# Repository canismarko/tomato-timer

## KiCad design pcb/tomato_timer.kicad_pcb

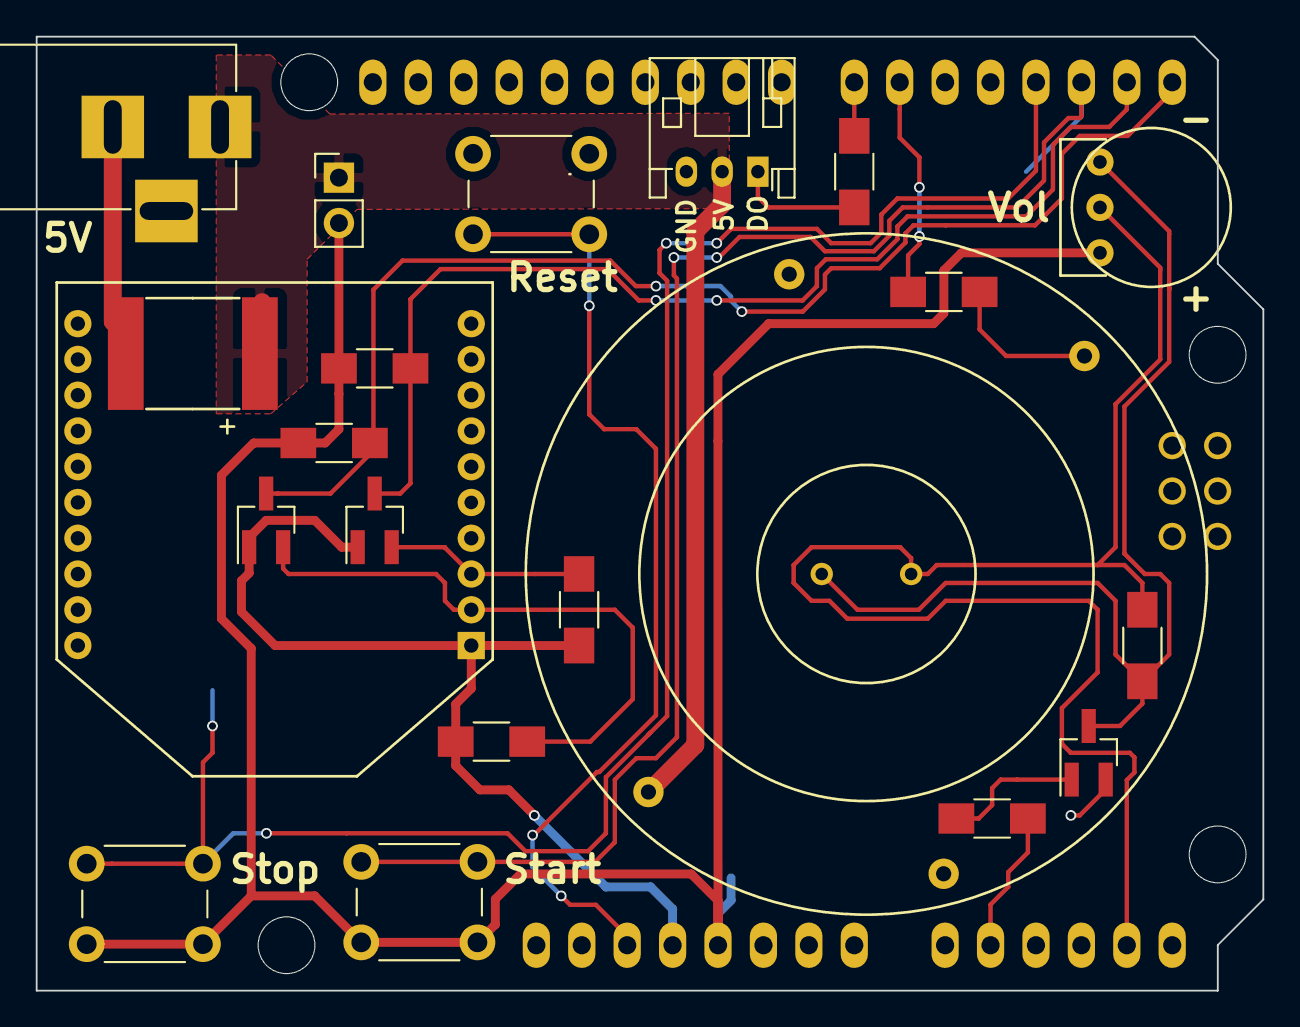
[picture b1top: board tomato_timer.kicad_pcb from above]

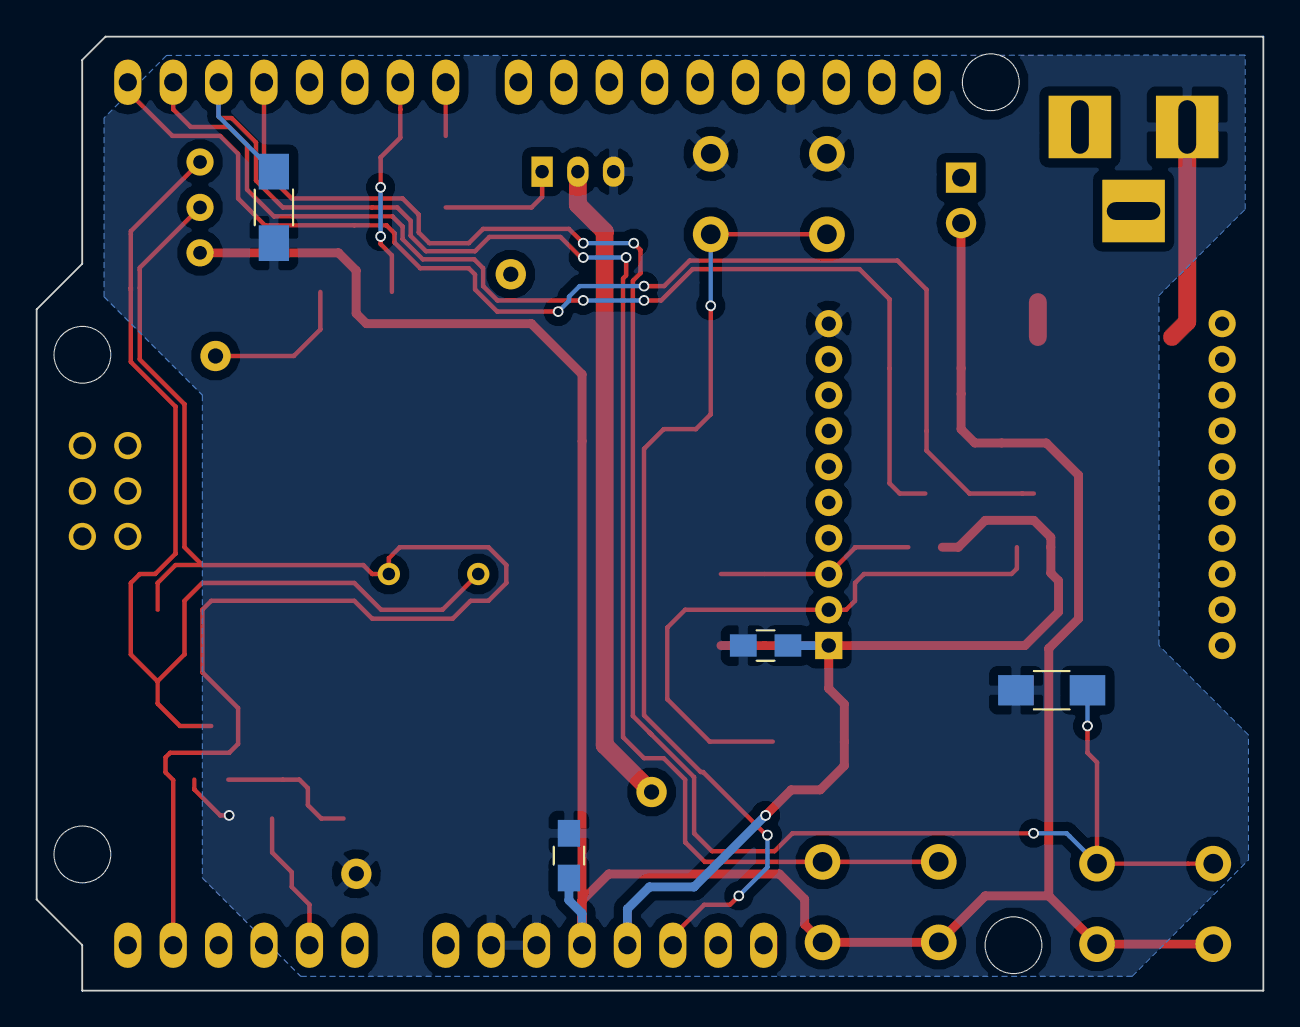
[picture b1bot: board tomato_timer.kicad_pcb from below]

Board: 2 copper layers, 68.6 x 53.3 mm, 27 parts (4 on the bottom side), 19 nets.

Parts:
C1, C3: 0.1uF; C_0805_HandSoldering
C2: 1000uF; SMD-2824
D1: NeoPixel_Strip; JST_PH_S3B-PH-K_03x2.00mm_Angled
D2: NeoPixelRing; NeoPixelRing_12
J1: External_Power; BARREL_JACK
JP2: Jumper_2_Open; Pin_Header_Straight_1x02_Pitch2.54mm
LS1: Speaker_Crystal; Buzzer160
Q1, Q2: BSS138; SOT-23_Handsoldering
Q3: TRANSISTOR_NPN; MMBT6428LT1G_NPN
R1, R2, R3, R4, R5, R6, R9: 10K; R_1206_HandSoldering
R7, R8: 470; R_1206_HandSoldering
R10: 1K; R_1206_HandSoldering
RV1: 10K; Whell_Potentiometer_3352T
SW2: SW_Reset; SW_PUSH_6mm
SW3: SW_Start; SW_PUSH_6mm
SW4: SW_Stop; SW_PUSH_6mm
TOMATO_SHIELD1: ARDUINO_SHIELD
U1: XBeeSeries1; XBee802.154.4

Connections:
/3V3: C1.2, Q1.1, Q2.1, R2.2, R4.2, TOMATO_SHIELD1.3V3, U1.1
/5V: C3.2, JP2.2, R1.1, R3.1, RV1.3, SW3.1, SW4.1, TOMATO_SHIELD1.5V
/5V_IN: C2.1, D1.2, D2.3, J1.1, JP2.1
/BTN_START: R5.1, SW3.2, TOMATO_SHIELD1.2
/BTN_STOP: R6.1, SW4.2, TOMATO_SHIELD1.3
/BUZZER: R9.1, TOMATO_SHIELD1.AD1
/DIN: Q1.2, R2.1, U1.3
/DOUT: Q2.2, R4.1, U1.2
/GND: C1.1, C2.2, C3.1, D1.3, D2.2, J1.2, Q3.E, R5.2, R6.2, SW2.2, TOMATO_SHIELD1.GND1, TOMATO_SHIELD1.GND2, TOMATO_SHIELD1.GND3, U1.10
/PIXEL_RING_PIN: R7.2, TOMATO_SHIELD1.6
/PIXEL_STRIP_PIN: R8.2, TOMATO_SHIELD1.7
/RESET: SW2.1, TOMATO_SHIELD1.RST
/RX: Q2.3, R3.2, TOMATO_SHIELD1.0
/TX: Q1.3, R1.2, TOMATO_SHIELD1.1
/VOL_IN: LS1.2, R10.1, RV1.2, TOMATO_SHIELD1.AD4
unnamed: D1.1, R8.1
unnamed: D2.4, R7.1
unnamed: LS1.1, Q3.C, R10.2, RV1.1
unnamed: Q3.B, R9.2

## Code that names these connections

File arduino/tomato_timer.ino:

/*
  Tomato Timer

  Creates a countdown timer for staying on track during boring work.

  Exampes usage: work for 25 min, then break for 5,
  then work for 25, etc. Every 4 work periods,
  there is a longer 20 minutes break.

  January 2017
  Mark Wolf
*/

// Durations for each phase (in milliseconds)
// Eg. 5 * 60 * 1000 --> 5 min
#define TICK  400
#define DEBUG_SPEEDUP 1 // Set to 1 for normal operation
#define WORK_TIME 25 * 60 * 1000ul / DEBUG_SPEEDUP
#define BREAK_TIME 5 * 60 * 1000ul / DEBUG_SPEEDUP
#define BREAK_TIME_LONG BREAK_TIME * 4

#define TONE_HZ 200

// Possible states for the system
#define WORKING 0
#define BREAK 1
#define LONG_BREAK 2
#define EXPIRED 3
#define STOPPED 4

// Button and buzzer pin assignments
#define BTN_START 2
#define BTN_STOP 3
// #define BTN_PIN 2
// #define BTN_STOP 19
// #define MUTE_PIN 2
#define BUZZER A0

// LED pin assignments
#define RED0 7
#define RED1 5
#define RED2 4
#define RED3 6
#define RED4 8
#define GRN0 10
#define GRN1 11
#define GRN2 12
#define GRN3 13
#define GRN4 9

// Define pins for the red and green LED's
const int N_REDS = 5;
const int RED_PINS[N_REDS] = {RED0, RED1, RED2, RED3, RED4};
const int N_GRNS = 5;
const int GRN_PINS[N_GRNS] = {GRN0, GRN1, GRN2, GRN3, GRN4};

// Variable for keeping track of how long this round has been running
unsigned long startTime;

// Variable to keep track of which round of work we're on
unsigned long currentRound;
bool isStopped; // Are we currently paused
bool volatile btnPressed;
bool volatile useBuzzer;
bool volatile stopRequested; // Is the system waiting for a stop button handler

// Function to keep track of when the button was pressed
void press_button() {
  Serial.print("Start button pressed\n");
  btnPressed = true;
}

void stop_pressed() {
  Serial.print("Stop requested\n");
  stopRequested = true;
}

// Function for advancing to the next round of work
void start_next_round() {
  // Flash the lights to indicate the round number
  if (currentRound > 0) {
    sound_buzzer(LOW);
    writeRedPins(LOW);
    writeGreenPins(LOW);
    delay(TICK / 2);
    for (int i=0; i < currentRound; i += 1) {
      sound_buzzer(HIGH);
      writeRedPins(HIGH);
      writeGreenPins(HIGH);
      delay(TICK / 5);
      sound_buzzer(LOW);
      writeRedPins(LOW);
      writeGreenPins(LOW);
      delay(TICK);
    }
    writeRedPins(LOW);
    writeGreenPins(LOW);
    delay(TICK / 5);
  }
  // Log to serial console
  Serial.print("Advancing to round ");
  Serial.print(currentRound);
  Serial.print("\n");
  // Update state variables
  isStopped = false;
  currentRound += 1;
  startTime = millis();
  btnPressed = false;
  useBuzzer = true;
  // Turn off buzzer and pause for a moment
  noTone(BUZZER);
  delay(2*TICK);
  // Keep track of state
  isStopped = false;
}


// Global variable for whether to sound the buzzer (gets reset every round)
void mute_buzzer() {
  Serial.print("Silencing buzzer\n");
  useBuzzer = false;
}

// Function that either turns on or turns off the buzzer
void sound_buzzer(int state) {
  if (state == HIGH && useBuzzer) {
    tone(BUZZER, TONE_HZ);
  } else {
    noTone(BUZZER);
  }
}


// Function sets all pins in an array
void writeRedPins(int state) {
  for (int i = 0; i < N_REDS; i += 1) {
    digitalWrite(RED_PINS[i], state);
  }
}


// Function sets all pins in an array
void writeGreenPins(int state) {
  for (int i = 0; i < N_GRNS; i += 1) {
    digitalWrite(GRN_PINS[i], state);
  }
}


// Function that fluorishes the lights, then waits for the user to press the "Go" button
void pauseInit() {
  Serial.print("Pausing init\n");
  // Cycle through the lights
  char pins[] = {RED0, RED1, RED2, RED3, RED4, GRN3, GRN2, GRN1, GRN0, GRN4};
  int pause = 30;
  for (char i=0; i<10; i++) {
    digitalWrite(pins[i], HIGH);
    delay(pause);
    digitalWrite(pins[i], LOW);
  }
  for (char i=9; i>-1; i--) {
    digitalWrite(pins[i], HIGH);
    delay(pause);
    digitalWrite(pins[i], LOW);
  }

  // Wait for user to press the go button
  while (!btnPressed) {
    delay(100);
  }
}


// the setup function runs once when you press reset or power the board
void setup() {
  Serial.begin(9600);
  // initialize digital pin LED_BUILTIN as an output.
  for (int i = 0; i < N_REDS; i++) {
    pinMode(RED_PINS[i], OUTPUT);
  }
  for (int i = 0; i < N_GRNS; i++) {
    pinMode(GRN_PINS[i], OUTPUT);
  }

  // Set the interrupt for when the various buttons are pressed
  // attachInterrupt(digitalPinToInterrupt(MUTE_PIN), mute_buzzer, RISING);
  attachInterrupt(digitalPinToInterrupt(BTN_START), press_button, RISING);
  attachInterrupt(digitalPinToInterrupt(BTN_STOP), stop_pressed, RISING);

  // Start of on the first round
  currentRound = 0;

  // Wait for the user to press the go button
  pauseInit();

  // And away we gooooo....
  startTime = millis();
}

// Function that returns the current state based on elapsed time for this round
int currentState() {
  unsigned long elapsed = millis() - startTime;
  // Variable for holding the output
  int state;
  // Variable for how long the break should be this time around
  unsigned long round_time;
  // Variable for which break period we're in
  int break_type;
  if (currentRound % 4) {
    // Regular short break
    round_time = WORK_TIME + BREAK_TIME;
    break_type = BREAK;
  } else {
    // Every fourth round is a long break
    round_time = WORK_TIME + BREAK_TIME_LONG;
    break_type = LONG_BREAK;
  }
  // Now see what phase we're in based on how long we've been running
  if (isStopped) {
    state = STOPPED;
  } else if (elapsed < WORK_TIME) {
    // Just regular old working mode
    state = WORKING;
  } else if (elapsed < round_time) {
    // We're in a break
    state = break_type;
  } else {
    // Break is over, and we need to get back to work!
    state = EXPIRED;
  }
  return state;
}


void loop() {

  // Set the appropriate LEDs
  int state = currentState();
  
  // Check if the user 
  if (btnPressed) {
    if (state == WORKING && currentRound > 0) {
      currentRound -= 1;
    }
    start_next_round();
  }



  unsigned long runTime = millis() - startTime;
  char tickPhase = (runTime) % (TICK * 2) / TICK;
  if (stopRequested) {
    Serial.print("Stopping\n");
    isStopped = true;
    stopRequested = false;
    sound_buzzer(LOW);
    writeGreenPins(LOW);
    writeRedPins(LOW);
    if (state == WORKING && currentRound > 0) {
      currentRound -= 1;
    }
    // Wait for the user to advance to the next round
    pauseInit();
    // And away we gooooo....
    startTime = millis();
  } else if (state == WORKING) {
    writeGreenPins(LOW);
    // Set the red LEDs
    int n_leds = (runTime) / (WORK_TIME / N_REDS) % N_REDS;
    for (char i=0; i<n_leds; i++) {
      // Unset the lower pins
      digitalWrite(RED_PINS[i], LOW);
    }
    for (char i=n_leds; i<N_REDS; i++) {
      // Set the upper pins
      digitalWrite(RED_PINS[i], HIGH);
    }
  } else if (state == BREAK) {
    writeRedPins(LOW);
    // Just set one green LED
    digitalWrite(GRN3, HIGH);
  } else if (state == LONG_BREAK) {
    // Set the green LEDs
    writeRedPins(LOW);
    // Set the green LEDs
    // int n_leds = (runTime - WORK_TIME) / (BREAK_TIME_LONG / N_GRNS) % N_GRNS;
    int n_leds = (runTime - WORK_TIME) / (BREAK_TIME_LONG / (N_GRNS-1)) % (N_GRNS-1);
    for (char i=0; i<n_leds; i++) {
      // Unset the lower pins
      digitalWrite(GRN_PINS[i], LOW);
    }
    for (char i=n_leds; i<(N_GRNS-1); i++) {
      // Set the upper pins
      digitalWrite(GRN_PINS[i], HIGH);
    }
  } else if (state == EXPIRED) {
    
    sound_buzzer(tickPhase);
    writeRedPins(tickPhase);
    writeGreenPins(LOW);
  }

  // Check if the buzzer should sound to alert that a break has just started
  if (runTime > WORK_TIME && runTime < WORK_TIME + 6*TICK) {
    sound_buzzer(tickPhase);
  } else if (state != EXPIRED) {
    sound_buzzer(LOW);
  }

  delay(TICK);
}

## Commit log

2019-01-29 Added gen 1 arduino code.
2019-01-29 Added PCB layout and Arduino code for generation 2.
2019-02-03 Updated the KiCad and Arduino files to use NeoPixel.
2019-02-03 Added basic footprints for neopixel ring and neopixel strip terminal block.
2019-02-05 Removed switch for external PS, and added pads to neopixel footprint.
2019-02-05 Re-worked the volume potentiometer for the buzzer.
2019-02-08 Picked remaning part footprints, and prepared board layout.
2019-02-12 Converted the buzzer to be controlled by a transistor and volume control by the pot wiper.
2019-02-24 Final board build used for fabrication.
2019-03-23 Re-wrote Arduino firmware for the new neopixel.
2019-05-06 Restored support for an external LED neopixel strip.
2019-06-10 Stop button now temporarily mutes the buzzer until the next round starts.
2020-10-27 Strip lights now cycle colors when not working.
